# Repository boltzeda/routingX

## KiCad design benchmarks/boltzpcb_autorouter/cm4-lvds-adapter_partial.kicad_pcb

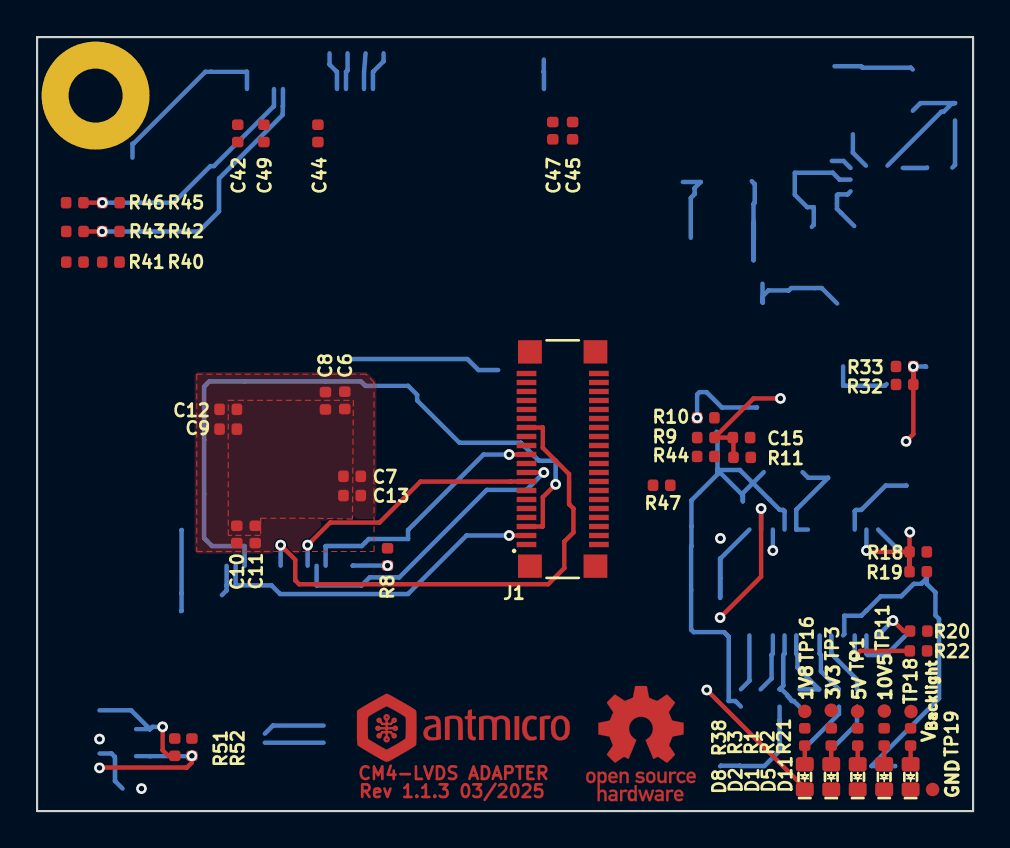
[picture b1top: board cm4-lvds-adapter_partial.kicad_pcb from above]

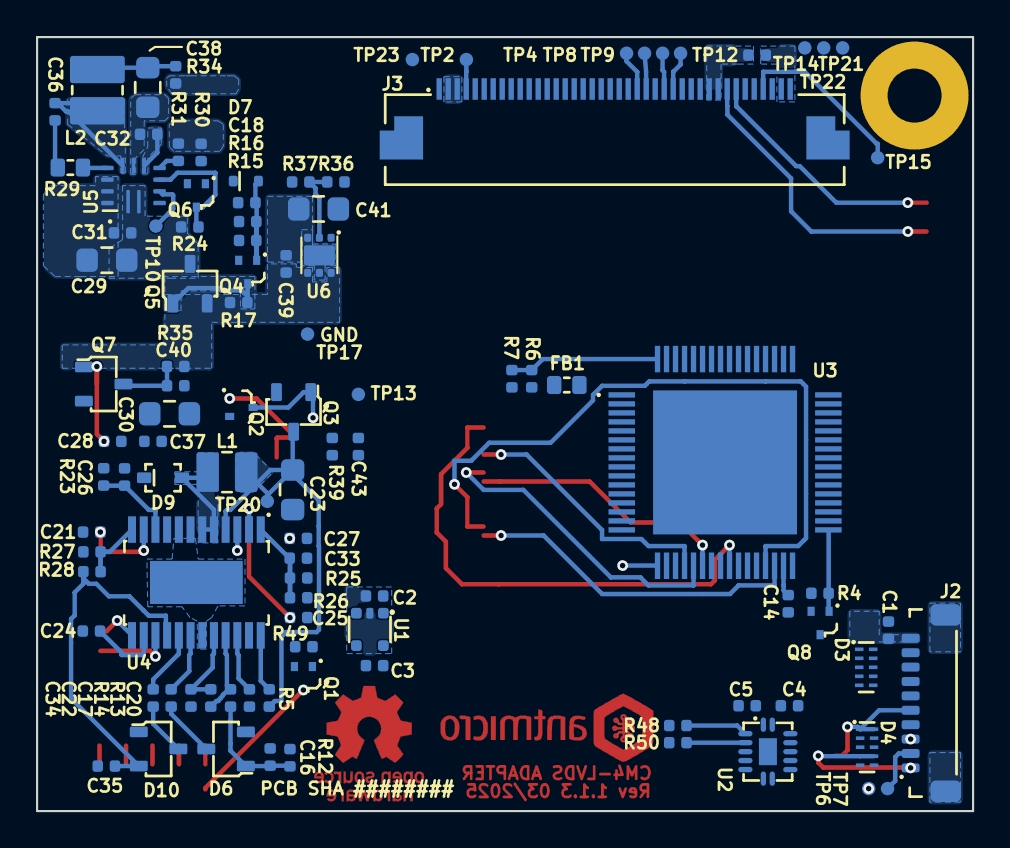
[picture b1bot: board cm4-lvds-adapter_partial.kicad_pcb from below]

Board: 6 copper layers, 52.0 x 43.0 mm, 153 parts (101 on the bottom side), 106 nets.

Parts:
C1, C6, C15: C_10u_0402; C_0402_1005Metric
C2, C3, C7, C14: C_1u_0402; C_0402_1005Metric
C4, C5, C8, C9, C10, C18, C27, C31, C32, C36, C42, C43, C44, C45, C46, C47, C49: C_100n_0402; C_0402_1005Metric
C11, C12, C13, C25: C_10n_0402; C_0402_1005Metric
C16, C22, C34, C35: C_330n_0402; C_0402_1005Metric
C17, C37: C_220n_16V_0402; C_0402_1005Metric
C20: C_2n2_0402; C_0402_1005Metric
C21: C_1n_0402; C_0402_1005Metric
C23, C29, C30, C38, C41: C_22u_25V_0805; C_0805_2012Metric
C24, C33: C_22p_0402; C_0402_1005Metric
C26, C28, C39, C40: C_1u_25V_0402; C_0402_1005Metric
D1, D2, D5, D8, D11: LED_G_0603_KP-1608ZGC; LED_0603_1608Metric_G
D3, D4: PUSB3F96X_PASS; Nexperia_DFN-10_2.5x1mm_P0.5mm
D6, D10: BAT54S-E3-08; SOT-23-3
D7: RB521S30T1G; SOD-523
D9: PMEG3010CEJ,115; D_SOD-323F
FB1: FB_220Z_2.2A_TDK-MPZ_0603; FB_0603_1608Metric
J1: Plug_Molex_SlimStack_2x20_556500488; Conn_Plug_Molex_SlimStack_2x20_556500488
J2: JST_SUR_1x10_SM10B-SURS-TF-LF-SN; Conn_JST_SUR_1x10_SM10B-SURS-TF-LF-SN
J3: FFC_Amphenol_1x40_62684-401100AHLF; Conn_FFC_Amphenol_1x40_62684-401100AHLF
L1: L_3u3_2.5A_1008; L_1008_2520Metric
L2: L_10u_0.5A_Murata-8200; L_Murata-8200
MP1: MP_Pad6mm_Drill3mm
Q1, Q2, Q4, Q6, Q8: PJE138K; SOT-523
Q3, Q5, Q7: SSM3J332R; SOT-23-3
R1, R38: R_470R_0402; R_0402_1005Metric
R2, R21: R_1k5_0402; R_0402_1005Metric
R3: R_100R_0402; R_0402_1005Metric
R4, R10, R11, R17, R26, R33, R44, R49: R_100k_0402; R_0402_1005Metric
R5, R12, R20, R22, R23, R34, R35, R41, R43, R46, R51, R52: R_0R_0402; R_0402_1005Metric
R6, R7, R8, R24, R37, R39, R40, R42, R45, R47, R48, R50: R_10k_0402; R_0402_1005Metric
R9: R_1k_0402; R_0402_1005Metric
R13, R19: R_590k_0402; R_0402_1005Metric
R14: R_120k_0402; R_0402_1005Metric
R15, R30: R_330k_0402; R_0402_1005Metric
R16: R_49k9_0402; R_0402_1005Metric
R18: R_1M_0402; R_0402_1005Metric
R25: R_820k_0402; R_0402_1005Metric
R27, R36: R_110k_0402; R_0402_1005Metric
R28: R_1M5_0402; R_0402_1005Metric
R29: R_20R_0603; R_0603_1608Metric
R31: R_1R2_0402; R_0402_1005Metric
R32: R_510k_0402; R_0402_1005Metric
TP1, TP2, TP3, TP4, TP6, TP7, TP8, TP9, TP10, TP11, TP12, TP13, TP14, TP15, TP16, TP17, TP18, TP19, TP20, TP21, TP22, TP23: TP_0.75mm_SMD; TP_SMD_0.75mm
U1: TLV70018_SC70; SC-70-5
U2: NTS0104_DHVQFN; DHVQFN-14-1EP_2.5x3mm
U3: SN65DSI84; HTQFP-64_10x10mm_P0.5mm
U4: TPS65150_HTSSOP; HTSSOP-24_W4.4mm_P0.65mm
U5: MPQ7235GQBE; QFN-13_2.5x3mm
U6: TLV76701_WSON; WSON-6-1EP_2x2mm_P0.65mm

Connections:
+1V8: C3.2, C5.2, FB1.1, Q1.1 (G), R6.2, R48.2, R49.1, R50.2, TP16.1, U1.5 (VOUT), U2.1 (VCC_A), U2.8 (OE)
+3V3: C2.2, C4.2, C47.2, J1.12, J3.2, J3.3, R3.2, R39.2, R40.2, R42.2, R44.2, R45.2, R47.2, TP3.1, U1.1 (VIN), U2.14 (VCC_B)
+3V9: C45.2, J3.1, R23.2, TP23.1
+5V: C1.2, D3.1 (CH1), D3.10 (CH1), J1.4, J1.6, J1.8, J1.10, J2.10, Q3.2 (S), R1.2, R10.2, R20.2, R38.2, TP1.1
+9V6: C41.1, C44.2, J3.29, R36.2, U6.1 (OUT)
+10V5: C39.2, Q5.2 (S), R2.2, R17.2, R18.2, R35.2, TP11.1, U6.4 (EN), U6.6 (IN)
+18V: C42.2, J3.38, R15.2, R22.2, TP22.1
+VLED: C46.2, J3.39, J3.40, R34.2
-6V: C49.2, J3.35, R12.2, TP21.1
-VLED: C46.1, J3.31, J3.32, R30.1, R31.2
/Antmicro CM4 Baseboard DSI Connector /DSI.CLK_N: J1.27, U3.25 (DACN)
/Antmicro CM4 Baseboard DSI Connector /DSI.CLK_P: J1.29, U3.24 (DACP)
/Antmicro CM4 Baseboard DSI Connector /DSI.D0_N: J1.21, U3.20 (DA0N)
/Antmicro CM4 Baseboard DSI Connector /DSI.D0_P: J1.23, U3.19 (DA0P)
/Antmicro CM4 Baseboard DSI Connector /DSI.D1_N: J1.15, U3.22 (DA1N)
/Antmicro CM4 Baseboard DSI Connector /DSI.D1_P: J1.17, U3.21 (DA1P)
/Antmicro CM4 Baseboard DSI Connector /DSI.D2_N: J1.9, U3.28 (DA2N)
/Antmicro CM4 Baseboard DSI Connector /DSI.D2_P: J1.11, U3.27 (DA2P)
/Antmicro CM4 Baseboard DSI Connector /DSI.D3_N: J1.3, U3.30 (DA3N)
/Antmicro CM4 Baseboard DSI Connector /DSI.D3_P: J1.5, U3.29 (DA3P)
/Antmicro CM4 Baseboard DSI Connector /DSICtrl.DIM: J1.28, Q6.1 (G)
/Antmicro CM4 Baseboard DSI Connector /DSICtrl.EN: D7.1 (C), J1.24, J3.6, R9.1, R44.1, U1.3 (EN), U2.11 (B3)
/Antmicro CM4 Baseboard DSI Connector /DSICtrl.GPIO: D4.2 (CH2), D4.9 (CH2), J1.30, J2.4
/Antmicro CM4 Baseboard DSI Connector /DSICtrl.SCL: D3.2 (CH2), D3.9 (CH2), J1.18, J2.9, U2.12 (B2)
/Antmicro CM4 Baseboard DSI Connector /DSICtrl.SDA: D3.4 (CH3), D3.7 (CH3), J1.16, J2.8, U2.13 (B1)
/Antmicro CM4 Baseboard DSI Connector /DSICtrl.~IRQ1: J1.20, Q8.3 (D), R47.1
/Antmicro CM4 Baseboard DSI Connector /DSICtrl.~IRQ2: D3.5 (CH4), D3.6 (CH4), J1.22, J2.7
/Antmicro CM4 Baseboard DSI Connector /DSICtrl.~RST: C43.2, J1.26, J3.5, R39.1, R51.1, R52.1, TP13.1
/DSI to LVDS/DSICtrl_1V8.EN: U2.4 (A3), U3.2 (EN)
/DSI to LVDS/DSICtrl_1V8.SCL: R50.1, U2.3 (A2), U3.15 (SCL)
/DSI to LVDS/DSICtrl_1V8.SDA: R48.1, U2.2 (A1), U3.16 (SDA)
/DSI to LVDS/LVDS.CLK_N: J3.17, U3.39 (A_CLKN)
/DSI to LVDS/LVDS.CLK_P: J3.18, U3.38 (A_CLKP)
/DSI to LVDS/LVDS.D0_N: J3.8, U3.47 (A_Y0N)
/DSI to LVDS/LVDS.D0_P: J3.9, U3.46 (A_Y0P)
/DSI to LVDS/LVDS.D1_N: J3.11, U3.45 (A_Y1N)
/DSI to LVDS/LVDS.D1_P: J3.12, U3.44 (A_Y1P)
/DSI to LVDS/LVDS.D2_N: J3.14, U3.42 (A_Y2N)
/DSI to LVDS/LVDS.D2_P: J3.15, U3.41 (A_Y2P)
/DSI to LVDS/LVDS.D3_N: J3.20, U3.37 (A_Y3N)
/DSI to LVDS/LVDS.D3_P: J3.21, U3.36 (A_Y3P)
/LVDS and Touchscreen Connectors/RST_TS: D4.1 (CH1), D4.10 (CH1), J2.5, R51.2
/LVDS and Touchscreen Connectors/SELB: J3.28, R40.1, R41.1
/LVDS and Touchscreen Connectors/SHLR: J3.33, R42.1, R43.1
/LVDS and Touchscreen Connectors/TP10_TS: D4.4 (CH3), D4.7 (CH3), J2.1, R52.2
/LVDS and Touchscreen Connectors/UPDN: J3.34, R45.1, R46.1
/Power/ADJ: C24.2, U4.14 (ADJ)
/Power/COMP: C20.2, U4.22 (COMP)
/Power/DLY1: C25.2, U4.2 (DLY1)
/Power/DLY2: C27.2, U4.3 (DLY2)
/Power/FDLY: R5.2, U4.24 (FDLY)
/Power/FLK: R20.1, U4.13 (CTRL)
/Power/Vi_{BOOST}: C23.1, L1.1, Q3.3 (D), R5.1, TP20.1, U4.4 (VIN)
GND: C1.1, C2.1, C3.1, C4.1, C5.1, C6.1, C7.1, C8.1, C9.1, C10.1, C11.1, C12.1, C13.1, C14.1, C15.1, C16.1, C17.1, C18.1, C20.1, C21.1, C23.2, C24.1, C25.1, C26.1, C27.1, C28.1, C29.2, C30.2, C31.1, C32.1, C35.1, C38.2, C39.1, C40.1, C41.2, C42.1, C43.1, C44.1, C45.1, C47.1, C49.1, D1.1 (C), D2.1 (C), D3.3 (GND), D3.8 (GND), D4.3 (GND), D4.5 (CH4), D4.6 (CH4), D4.8 (GND), D5.1 (C), D6.2, D11.1 (C), J1.1, J1.2, J1.7, J1.13, J1.14, J1.19, J1.25, J1.31, J1.32, J1.MP, J2.6, J2.MP, J3.7, J3.10, J3.13, J3.16, J3.19, J3.22, J3.25, J3.30, J3.SH, MP1.1, Q1.2 (S), Q2.2 (S), Q4.2 (S), Q6.2 (S), Q8.2 (S), R4.2, R7.1, R8.2, R11.1, R16.1, R19.1, R26.1, R27.1, R31.1, R37.1, R41.2, R43.2, R46.2, R49.2, TP17.1, TP19.1, U1.2 (GND), U2.7 (GND), U2.15 (GNDPAD), U3.23 (GND), U3.26 (GND), U3.52 (GND), U3.65 (PAD), U4.7 (PGND), U4.8 (PGND), U4.19 (AGND), U4.25 (EP), U5.8 (GND), U5.11 (GND), U5.12 (GND), U5.13 (GND), U6.3 (GND), U6.5 (GND), U6.7 (PAD)
unnamed: C6.2, C7.2, C8.2, C9.2, C10.2, C11.2, C12.2, C13.2, FB1.2, U3.3 (VCC), U3.14 (VCC), U3.18 (VCC), U3.32 (VCC), U3.35 (VCC), U3.40 (VCC), U3.43 (VCC), U3.48 (VCC), U3.49 (VCC), U3.55 (VCC), U3.58 (VCC), U3.63 (VCC)
unnamed: C16.2, D6.1, R12.1, R13.2
unnamed: C22.2, D6.3
unnamed: C34.1, D10.3
unnamed: C36.2, R29.2
unnamed: C38.1, L2.2, R34.1
unnamed: D1.2 (A), R1.1
unnamed: D2.2 (A), R3.1
unnamed: D5.2 (A), R2.1
unnamed: C18.2, D7.2 (A), Q4.1 (G), R15.1, R16.2
unnamed: D8.2 (A), R38.1
unnamed: D8.1 (C), Q1.3 (D)
unnamed: D9.2 (A), L1.2, U4.5 (SW), U4.6 (SW)
unnamed: C28.2, C30.1, C33.2, C37.2, D9.1 (C), D10.1, Q7.2 (S), R25.2, R32.2, U4.9 (SUP)
unnamed: D11.2 (A), R21.1
unnamed: J2.2, TP7.1
unnamed: J2.3, TP6.1
unnamed: J3.4, TP2.1
unnamed: J3.23, TP4.1
unnamed: J3.24, TP8.1
unnamed: J3.26, TP9.1
unnamed: J3.27, TP12.1
unnamed: J3.36, TP14.1
unnamed: J3.37, TP15.1
unnamed: Q2.3 (D), Q3.1 (G), R10.1
unnamed: C15.2, Q2.1 (G), R9.2, R11.2
unnamed: Q4.3 (D), Q5.1 (G), R17.1
unnamed: C29.1, C31.2, Q5.3 (D), R21.2, R24.2, TP18.1, U5.1 (IN), U5.2 (IN)
unnamed: Q6.3 (D), R24.1, U5.5 (DIM)
unnamed: C40.2, Q7.3 (D), R35.1
unnamed: C37.1, Q7.1 (G), R32.1, R33.2
unnamed: Q8.1 (G), R4.1, U3.33 (IRQ)
unnamed: R6.1, R7.2, U3.64 (ADDR)
unnamed: R8.1, U3.17 (REFCLK)
unnamed: C14.2, U3.31 (VCORE)
unnamed: C35.2, D10.2, R28.2, U4.16 (CPI)
unnamed: C22.1, U4.18 (DRVN)
unnamed: C34.2, U4.17 (DRVP)
unnamed: C33.1, R25.1, R26.2, U4.1 (FB)
unnamed: R13.1, R14.2, U4.21 (FBN)
unnamed: R27.2, R28.1, U4.12 (FBP)
unnamed: R33.1, U4.23 (GD)
unnamed: C21.2, R18.1, R19.2, U4.11 (IN)
unnamed: C17.2, R14.1, U4.20 (REF)
unnamed: C26.2, R23.1, U4.10 (VCOM)
unnamed: R22.1, U4.15 (VGH)
unnamed: R29.1, U5.10 (BST)
unnamed: R30.2, U5.6 (FB)
unnamed: C36.1, L2.1, U5.9 (SW)
unnamed: C32.2, U5.7 (V_{CC})
unnamed: TP10.1, U5.4 (~FAULT)
unnamed: R36.1, R37.2, U6.2 (FB)

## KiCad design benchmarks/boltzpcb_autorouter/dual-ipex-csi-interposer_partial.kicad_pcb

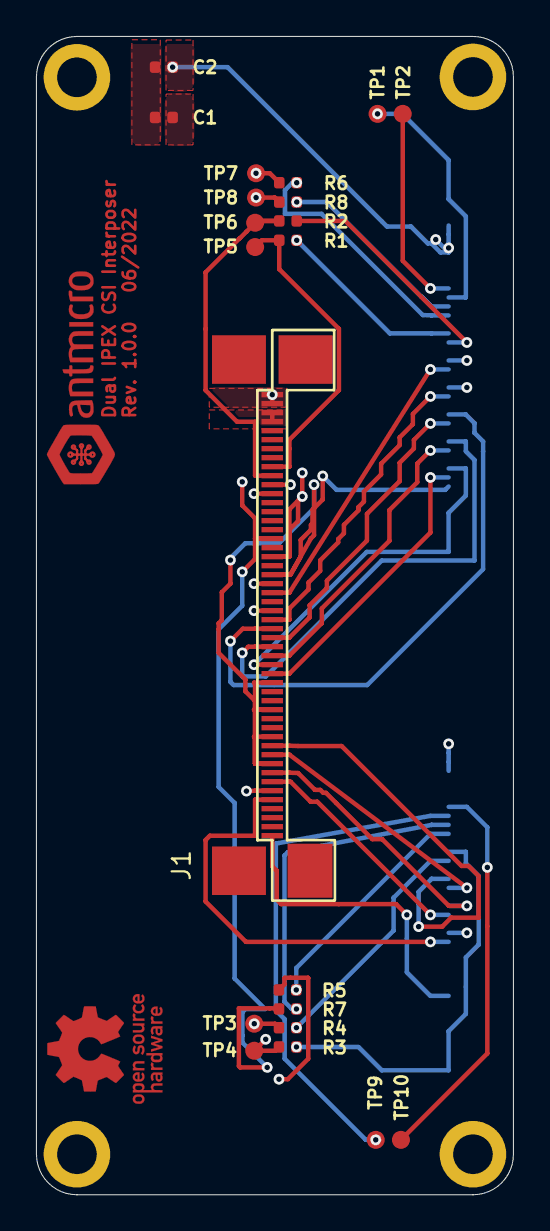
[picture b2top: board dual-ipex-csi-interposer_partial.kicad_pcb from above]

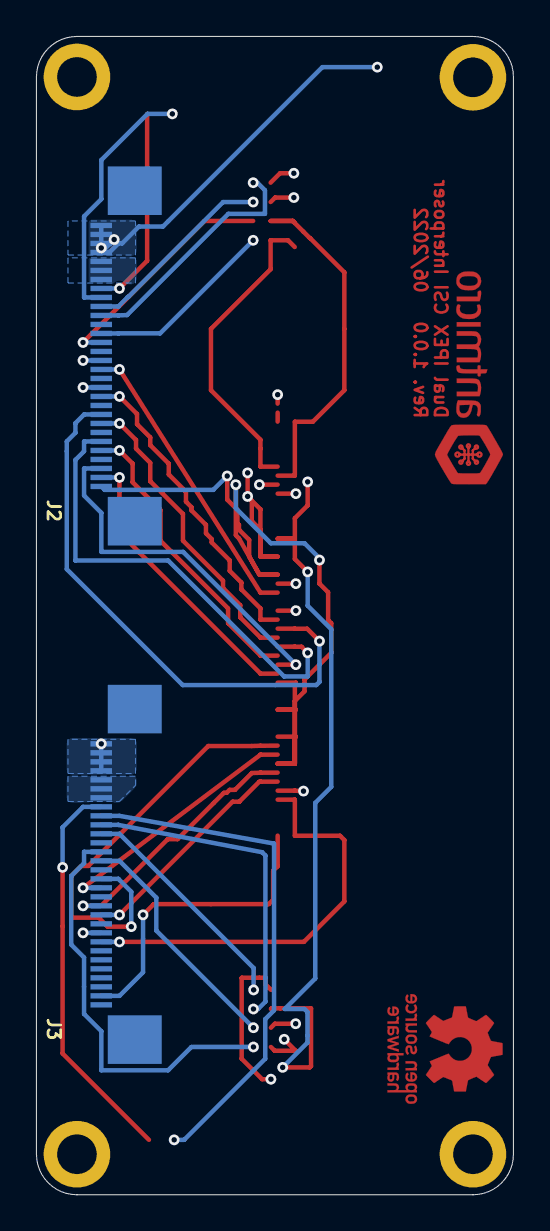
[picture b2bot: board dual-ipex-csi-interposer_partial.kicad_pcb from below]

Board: 4 copper layers, 26.5 x 64.3 mm, 29 parts (2 on the bottom side), 41 nets.

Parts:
C1, C2: C_100n_0402; 0402-cap
J1: WE_68715014522
J2, J3: MSAK24025P30
MP1, MP2, MP3, MP4: PCB_Mount_Hole_2.2_4.5; mounting-hole-2.2mm
N1: oshw_logo; oshw-logo
N2: antmicro_logo; antmicro-logo_scaled_12mm
R1, R2, R3, R4, R5, R6, R7, R8: R_0R_0402; 0402-res
TP1, TP2, TP3, TP4, TP5, TP6, TP7, TP8, TP9, TP10: TP_SMD1MM; Testpoint_smd_1mm

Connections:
3V3_FFC: C1.1, J1.47, J1.48, J2.24, J2.25, J2.26, J3.24, J3.25, J3.26
5V0_SYS: C2.1, J1.49, J1.50, J2.27, J2.28, J2.29, J2.30, J3.27, J3.28, J3.29, J3.30
/CAM_CSI_CAM_EN: J1.32, R5.2, R6.2, TP7.1
/CAM_CSI_CAM_XVS: J1.34, R7.2, R8.2, TP8.1
/CAM_L_SCL: J1.40, R3.2, TP4.1
/CAM_L_SDA: J1.39, R4.2, TP3.1
/CAM_R_SCL: J1.42, R1.2, TP5.1
/CAM_R_SDA: J1.41, R2.2, TP6.1
CAM1_CSI_CAM_CLK: J2.22, TP1.1
CAM1_CSI_CAM_EN: J2.20, R6.1
CAM1_CSI_CAM_XTRIG: J2.23, TP2.1
CAM1_CSI_CAM_XVS: J2.21, R8.1
CAM1_CSI_CLK_N: J1.28, J2.14
CAM1_CSI_CLK_P: J1.29, J2.15
CAM1_CSI_D0_N: J1.25, J2.11
CAM1_CSI_D0_P: J1.26, J2.12
CAM1_CSI_D1_N: J1.23, J2.8
CAM1_CSI_D1_P: J1.24, J2.9
CAM1_CSI_D2_N: J1.21, J2.5
CAM1_CSI_D2_P: J1.22, J2.6
CAM1_CSI_D3_N: J1.19, J2.2
CAM1_CSI_D3_P: J1.20, J2.3
CAM1_SCL: J2.18, R1.1
CAM1_SDA: J2.17, R2.1
CAM2_CSI_CAM_CLK: J3.22, TP9.1
CAM2_CSI_CAM_EN: J3.20, R5.1
CAM2_CSI_CAM_XTRIG: J3.23, TP10.1
CAM2_CSI_CAM_XVS: J3.21, R7.1
CAM2_CSI_CLK_N: J1.10, J3.14
CAM2_CSI_CLK_P: J1.11, J3.15
CAM2_CSI_D0_N: J1.7, J3.11
CAM2_CSI_D0_P: J1.8, J3.12
CAM2_CSI_D1_N: J1.5, J3.8
CAM2_CSI_D1_P: J1.6, J3.9
CAM2_CSI_D2_N: J1.3, J3.5
CAM2_CSI_D2_P: J1.4, J3.6
CAM2_CSI_D3_N: J1.1, J3.2
CAM2_CSI_D3_P: J1.2, J3.3
CAM2_SCL: J3.18, R3.1
CAM2_SDA: J3.17, R4.1
GND: C1.2, C2.2, J1.9, J1.12, J1.15, J1.18, J1.27, J1.30, J2.1, J2.4, J2.7, J2.10, J2.13, J2.16, J2.19, J3.1, J3.4, J3.7, J3.10, J3.13, J3.16, J3.19

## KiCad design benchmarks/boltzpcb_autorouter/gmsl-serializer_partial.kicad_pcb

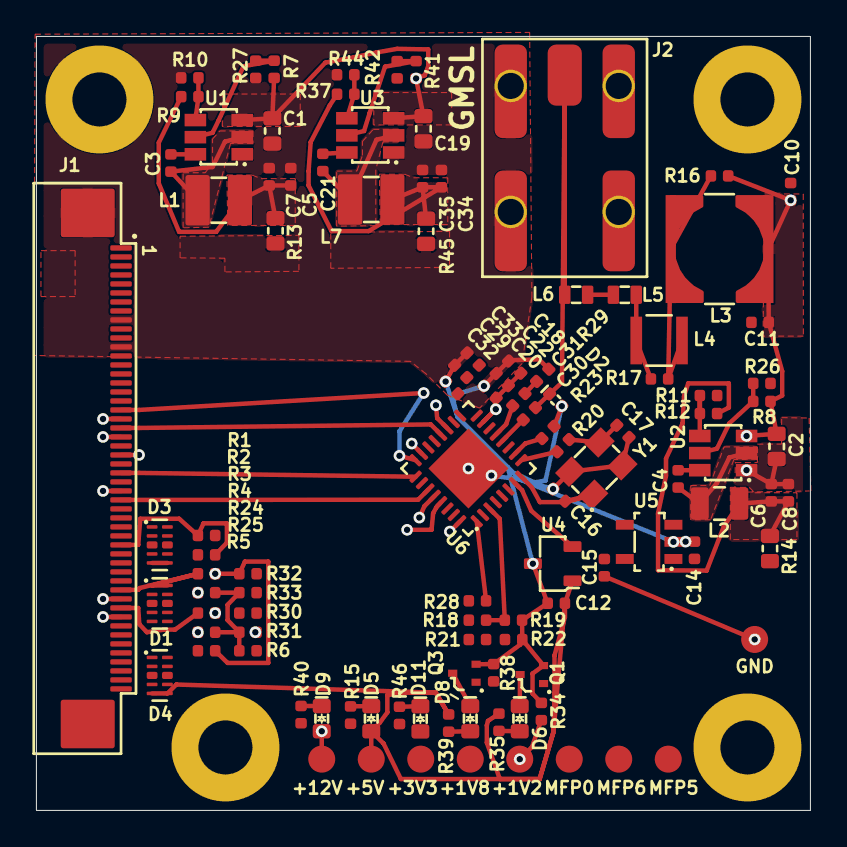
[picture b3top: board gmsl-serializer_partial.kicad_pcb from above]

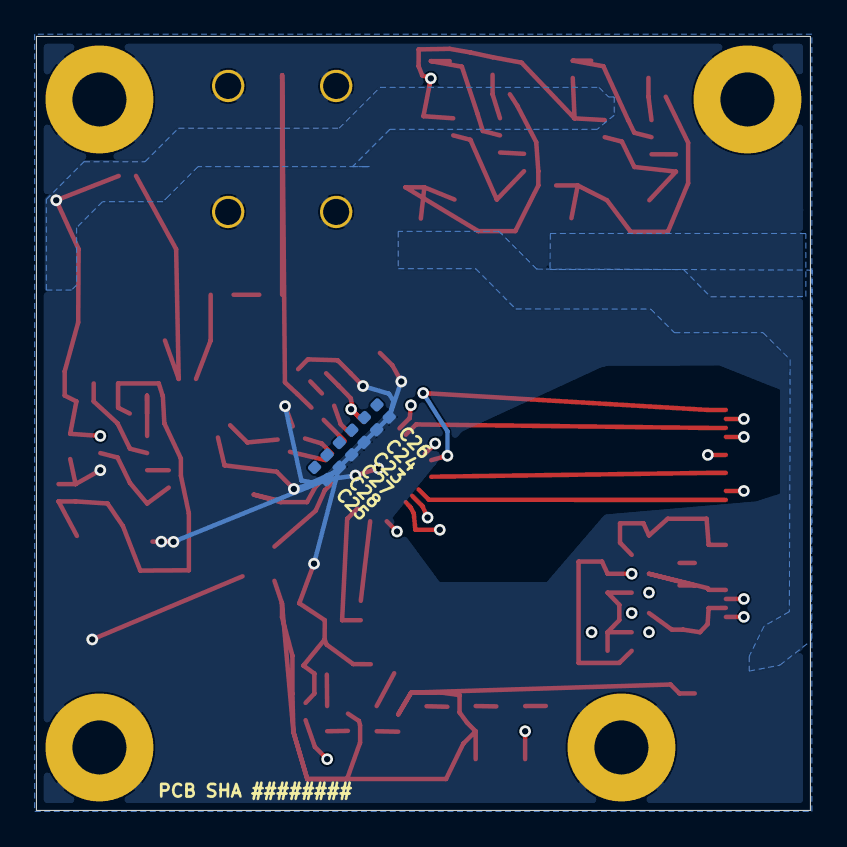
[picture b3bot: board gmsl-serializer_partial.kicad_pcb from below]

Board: 4 copper layers, 43.0 x 43.0 mm, 118 parts (6 on the bottom side), 70 nets.

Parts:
C1, C2, C19: C_10u_25V_0603; C_0603_1608Metric
C3, C21: C_220n_0402; C_0402_1005Metric
C4, C10, C20, C22, C24, C30, C31: C_100n_0402; C_0402_1005Metric
C5, C6, C7, C8, C34, C35: C_22u_0402; C_0402_1005Metric
C11, C23, C27, C28, C29, C32: C_10n_0402; C_0402_1005Metric
C12, C14, C15: C_1u_16V_0402; C_0402_1005Metric
C16, C17: C_33p_0402; C_0402_1005Metric
C18, C25, C26, C33: C_10u_0402; C_0402_1005Metric
D1, D3, D4: PESD4USB5U-TTS; DFN-10_2.5x1mm
D2: AXGD10402KR; D_0402_1005Metric
D5, D6, D8, D9, D11: LED_G_0603_LTST-C190GKT; LED_0603_1608Metric_G
J1: Conn_FFC_WE_68715014022; Conn_FFC_WE_68715014x22
J2: Conn_FAKRA_59S2AQ-40MT5-Z_1
L1, L7: L_3u3_3.1A_Bourns-SRP3212A; L_Bourns-SRP3212A
L2: L_1u_2.6A_0806; L_0806_2016Metric
L3: L_22u_1.12A_Coilcraft-MSS6132T; L_Coilcraft-MSS6132T
L4: L_6u8_1A_Coilcraft-1210POC; L_Coilcraft-1210POC
L5, L6: L_470n_1A_Coilcraft-PFL1609; L_Coilcraft-PFL1609
MP1, MP2, MP3, MP4: MP_Pad6mm_Drill3mm
N1: antmicro_logo; antmicro-logo_scaled_12mm_mask
Q1, Q3: DMG1012T-7; SOT-523
R1, R7, R8, R10, R12, R19, R21, R22, R26, R27, R28, R41, R42, R44: R_10k_0402; R_0402_1005Metric
R2: R_12k_0402; R_0402_1005Metric
R3, R4, R24, R25: R_100R_0402; R_0402_1005Metric
R5, R6: R_4k7_0402; R_0402_1005Metric
R9: R_52k3_0402; R_0402_1005Metric
R11: R_12k4_0402; R_0402_1005Metric
R13, R14, R45: R_0R_22.4A_0603; R_0603_1608Metric
R15, R35, R39: R_470R_0402; R_0402_1005Metric
R16, R17: R_5k1_0402; R_0402_1005Metric
R18: R_80k6_0402; R_0402_1005Metric
R20, R30, R31, R32, R33: R_0R_0402; R_0402_1005Metric
R23: R_402R_0402; R_0402_1005Metric
R29: R_51R_0402; R_0402_1005Metric
R34, R38: R_100k_0402; R_0402_1005Metric
R37: R_31k6_0402; R_0402_1005Metric
R40: R_1k65_0402; R_0402_1005Metric
R46: R_200R_0402; R_0402_1005Metric
TP1, TP2, TP3, TP4, TP5, TP6, TP7, TP8, TP9: TP_1.5mm_SMD; TP_SMD_1.5mm
U1, U2, U3: AP62301_TSOT; TSOT23-6
U4: REF3012AIDBZT; SOT-23-3
U5: TLV73312PDBVT; SOT-23-5
U6: MAX96717GTJ_VY+; TQFN-32-1EP_5x5mm_P0.5mm
Y1: Resonator_25MHz_ABM8G; Resonator_SMD_Abracon_ABM8G_3.2x2.5mm

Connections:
+1V2: C15.2, C18.2, C20.2, C22.2, Q1.1 (G), R34.2, TP5.1, U5.5 (VOUT), U6.15 (VDD)
+1V8: C14.2, C25.2, C27.2, C28.2, Q3.1 (G), R14.2, R38.2, TP2.1, U5.1 (VIN), U5.3 (EN), U6.11 (VDD18)
+3V3: C29.2, C32.2, C33.2, D4.1, D4.2, D4.9, D4.10, D11.2 (A), J1.47, J1.48, R5.2, R6.2, R18.2, R21.2, R28.2, R45.2, TP4.1, U6.16 (VDDIO)
+5V: C12.2, D4.4, D4.5, D4.6, D4.7, D5.2 (A), J1.49, J1.50, R13.2, R35.2, R39.2, TP1.1, U4.1 (IN)
+12V: C1.2, C2.2, C10.2, C11.2, C19.2, D9.2 (A), L3.1, R7.2, R8.2, R16.1, R41.2, TP3.1, U1.3 (VIN), U2.3 (VIN), U3.3 (VIN)
/CSI Connector/CSI.CLK_N: J1.28, U6.28 (CKN)
/CSI Connector/CSI.CLK_P: J1.29, U6.27 (CKP)
/CSI Connector/CSI.D0_N: J1.25, U6.26 (D0N)
/CSI Connector/CSI.D0_P: J1.26, U6.25 (D0P)
/CSI Connector/CSI.D1_N: J1.23, U6.30 (D1N)
/CSI Connector/CSI.D1_P: J1.24, U6.29 (D1P)
/CSI Connector/CSI.D2_N: J1.21, U6.20 (D2N)
/CSI Connector/CSI.D2_P: J1.22, U6.19 (D2P)
/CSI Connector/CSI.D3_N: J1.19, U6.24 (D3N)
/CSI Connector/CSI.D3_P: J1.20, U6.23 (D3P)
/CSI Connector/GPIO3: D3.1, D3.10, J1.32, U6.17 (MFP3)
/CSI Connector/GPIO4: R1.2, U6.18 (MFP4)
/CSI Connector/GPIO4_1V8: D3.2, D3.9, J1.34, R1.1, R2.1
/CSI Connector/I2C.SCL: R4.2, R6.1, R25.2, R31.1, R33.1
/CSI Connector/I2C.SDA: R3.2, R5.1, R24.2, R30.1, R32.1
/CSI Connector/SCL_CAM0: D1.2, D1.9, J1.40, R4.1
/CSI Connector/SCL_CAM1: D1.5, D1.6, J1.42, R25.1
/CSI Connector/SDA_CAM0: D1.1, D1.10, J1.39, R3.1
/CSI Connector/SDA_CAM1: D1.4, D1.7, J1.41, R24.1
/GMSL Connector/SIO_P: C30.2, D2.1 (C), J2.1, L6.2
/Serializer/CFG0: R18.1, R19.2, U6.3 (MFP1)
/Serializer/CFG1: R21.1, R22.2, U6.4 (MFP2)
/Serializer/VREF: U4.2 (OUT), U6.7 (VREF)
/Serializer/X1: C16.2, U6.8 (X1/OSC), Y1.1
/Serializer/X2: R20.2, U6.9 (X2)
/Serializer/X2_R: C17.2, R20.1, Y1.3
/Supply/EN_1V8: R8.1, R26.2, U2.5 (EN)
/Supply/EN_3V3: R41.1, R42.2, U3.5 (EN)
/Supply/EN_5V: R7.1, R27.2, U1.5 (EN)
/Supply/FB_1V8: R11.1, R12.2, U2.4 (FB)
/Supply/FB_3V3: R37.1, R44.2, U3.4 (FB)
/Supply/FB_5V: R9.1, R10.2, U1.4 (FB)
/Supply/OUT_1V8: C6.2, C8.2, L2.2, R11.2, R14.1
/Supply/OUT_3V3: C34.2, C35.2, L7.2, R37.2, R45.1
/Supply/OUT_5V: C5.2, C7.2, L1.2, R9.2, R13.1
/Supply/SW_1V8: C4.2, L2.1, U2.2 (SW)
/Supply/SW_3V3: C21.2, L7.1, U3.2 (SW)
/Supply/SW_5V: C3.2, L1.1, U1.2 (SW)
GND: C1.1, C2.1, C5.1, C6.1, C7.1, C8.1, C10.1, C11.1, C12.1, C14.1, C15.1, C16.1, C17.1, C18.1, C19.1, C20.1, C22.1, C23.1, C24.1, C25.1, C26.1, C27.1, C28.1, C29.1, C32.1, C33.1, C34.1, C35.1, D1.3, D1.8, D2.2 (A), D3.3, D3.8, D4.3, D4.8, J1.9, J1.12, J1.15, J1.18, J1.27, J1.30, J1.MP1 (MP), J1.MP2 (MP), J2.2, J2.3, J2.4, J2.5, MP1.1, MP2.1, MP3.1, MP4.1, Q1.2 (S), Q3.2 (S), R2.2, R10.1, R12.1, R15.1, R19.1, R22.1, R23.1, R26.1, R27.1, R29.1, R34.1, R38.1, R40.1, R42.1, R44.1, R46.1, TP9.1, U1.1 (GND), U2.1 (GND), U3.1 (GND), U4.3 (GND), U5.2 (GND), U6.33 (GND), Y1.2 (SH), Y1.4 (SH)
unnamed: C31.2, R29.2
unnamed: D5.1 (C), R15.2
unnamed: D6.2 (A), R35.1
unnamed: D6.1 (C), Q1.3 (D)
unnamed: D8.2 (A), R39.1
unnamed: D8.1 (C), Q3.3 (D)
unnamed: D9.1 (C), R40.2
unnamed: D11.1 (C), R46.2
unnamed: L3.2, L4.1, R16.2, R17.1
unnamed: L4.2, L5.1, R17.2
unnamed: L5.2, L6.1
unnamed: C3.1, U1.6 (BST)
unnamed: C4.1, U2.6 (BST)
unnamed: C21.1, U3.6 (BST)
unnamed: C23.2, C24.2, C26.2, U6.14 (CAP_VDD)
unnamed: TP6.1, U6.2 (MFP0)
unnamed: TP7.1, U6.21 (MFP5)
unnamed: TP8.1, U6.22 (MFP6)
unnamed: R30.2, U6.31 (MFP7)
unnamed: R31.2, U6.32 (MFP8)
unnamed: R32.2, U6.5 (MFP9)
unnamed: R33.2, U6.6 (MFP10)
unnamed: R28.1, U6.1 (PWDNB)
unnamed: C31.1, U6.13 (SION)
unnamed: C30.1, U6.12 (SIOP)
unnamed: R23.2, U6.10 (XRES)

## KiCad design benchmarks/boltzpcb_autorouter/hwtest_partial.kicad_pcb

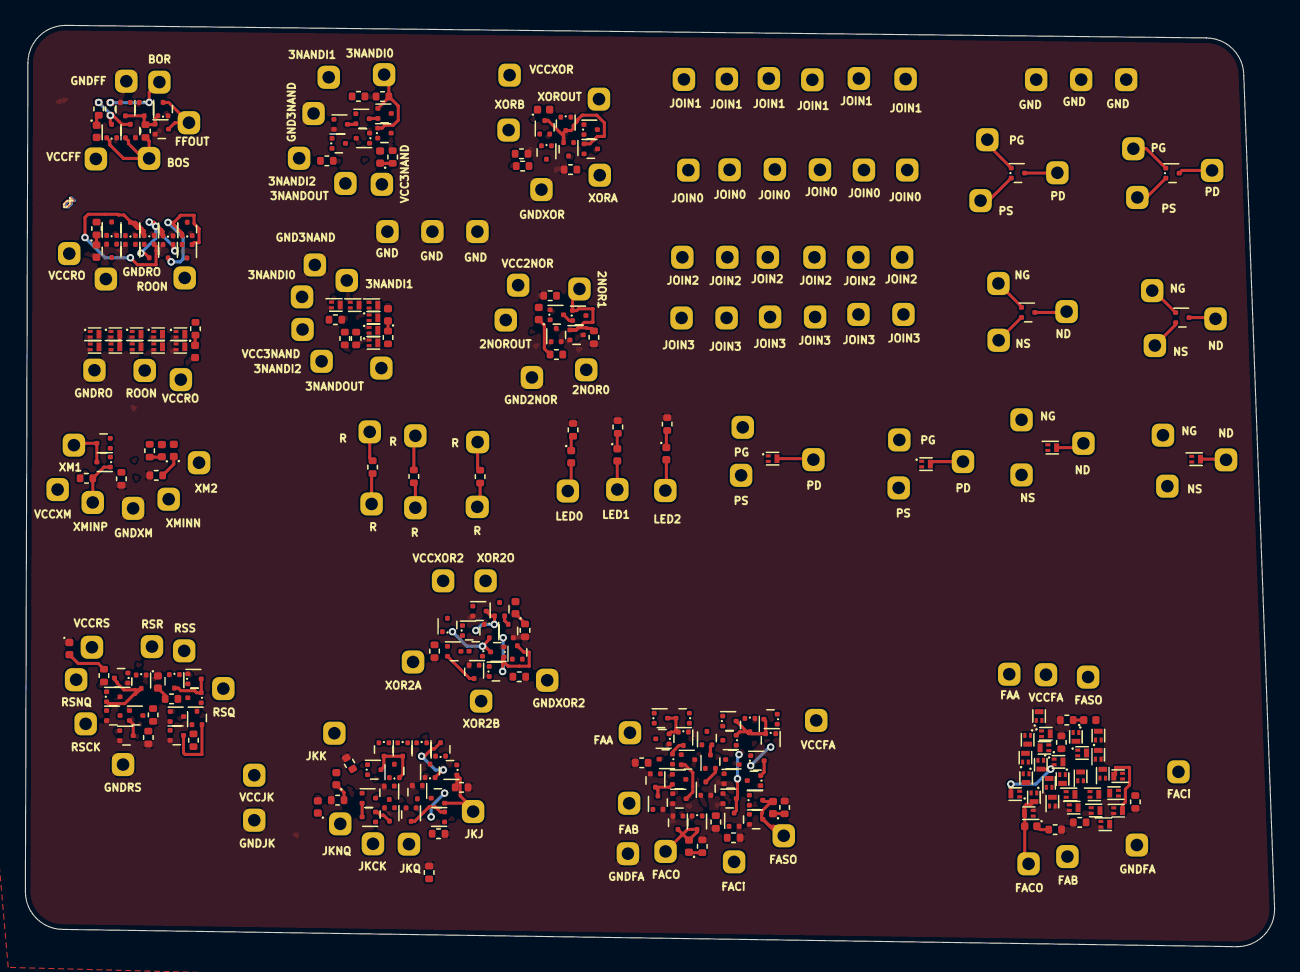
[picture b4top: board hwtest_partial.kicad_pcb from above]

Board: 2 copper layers, 99.7 x 73.5 mm, 362 parts (0 on the bottom side), 161 nets.

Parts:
D1, D2, D3, D4, D5, D6, D7, D8, D9, D10, D11, D12, D13, D14, D15, D16, D17, D18, D19, D20, D21: LED; LED_0402_1005Metric_COMPACT
N1, N2, N3, N4, N5, N6, N7, N8, N14, N15, N16, N20, N21, N22, N23, N24, N25, N26, N27, N30, N31, N32, N33, N34, N35, N36, N37, N38, N39, N40, N41, N42, N43, N44, N45, N46, N47, N48, N49, N50, N51, N52, N53, N54, N55, N56, N57, N58, N59, N60, N61, N62, N63: 2SK3541; SOT-723-COMPACT
N9, N10, N11, N12, N13, N17, N18, N19, N28, N29: NX7002BKMB315; DFN1006-3-NCH
N64, N65, N66, N67, N68, N69, N70, N71, N72, N73, N74, N75, N76, N77: 2SK3541; DFN1006-3-NCH
P1, P2, P3, P4, P5, P6, P7, P8, P14, P15, P16, P20, P21, P22, P23, P24, P25, P26, P27, P30, P31, P32, P33, P34, P35, P36, P37, P38, P39, P40, P41, P42, P43, P44, P45, P46, P47, P48, P49, P50, P51, P52, P53, P54, P55, P56, P57, P58, P59, P60, P61, P62, P63: RZM001P02T2L; SOT-723-COMPACTP
P9, P10, P11, P12, P13, P17, P18, P19, P28, P29: BSS84KNC; DFN1006-3-PCH
P64, P65, P66, P67, P68, P69, P70, P71, P72, P73, P74, P75, P76, P77: RZM001P02T2L; DFN1006-3-PCH
R1, R2, R3, R4, R5, R6, R7, R8, R9, R10, R11, R12, R13, R14, R15, R16, R17, R18, R19, R20, R21, R22, R23, R24, R25, R26, R27, R28, R29, R30, R31, R32, R33, R34, R35, R36, R37, R38, R39, R40, R41, R42, R43, R44, R45, R46, R47, R48, R49, R50, R51, R52: 1k; R_0402_1005Metric_COMPACT
TP1: BOS; TPTHRU
TP2: BOR; TPTHRU
TP3: FFOUT; TPTHRU
TP4, TP11: ROON; TPTHRU
TP5: VCCFF; TPTHRU
TP6: GNDFF; TPTHRU
TP7, TP9: GNDRO; TPTHRU
TP8, TP10: VCCRO; TPTHRU
TP12, TP21: 3NANDOUT; TPTHRU
TP13, TP19: 3NANDI0; TPTHRU
TP14, TP18: 3NANDI1; TPTHRU
TP15, TP20: 3NANDI2; TPTHRU
TP16, TP22: VCC3NAND; TPTHRU
TP17, TP23: GND3NAND; TPTHRU
TP24: 2NOR1; TPTHRU
TP25: 2NOR0; TPTHRU
TP26: 2NOROUT; TPTHRU
TP27: VCC2NOR; TPTHRU
TP28: GND2NOR; TPTHRU
TP29: XORB; TPTHRU
TP30: XM1; TPTHRU
TP31: XM2; TPTHRU
TP32: XMINP; TPTHRU
TP33: XMINN; TPTHRU
TP34: XORA; TPTHRU
TP35: VCCXM; TPTHRU
TP36: GNDXM; TPTHRU
TP37: XOROUT; TPTHRU
TP38: VCCXOR; TPTHRU
TP39: GNDXOR; TPTHRU
TP40: LED0; TPTHRU
TP41: LED1; TPTHRU
TP42: LED2; TPTHRU
TP43, TP68, TP74, TP80: PS; TPTHRU
TP44, TP67, TP73, TP79: PG; TPTHRU
TP45, TP69, TP75, TP81: PD; TPTHRU
TP46, TP71, TP77, TP83: ND; TPTHRU
TP47, TP72, TP78, TP84: NS; TPTHRU
TP48, TP70, TP76, TP82: NG; TPTHRU
TP49, TP50, TP51, TP52, TP53, TP54: R; TPTHRU
TP55, TP56, TP57, TP58, TP59, TP60: JOIN0; TPTHRU
TP61, TP62, TP63, TP64, TP65, TP66: JOIN1; TPTHRU
TP85, TP86, TP87, TP88, TP89, TP90: JOIN2; TPTHRU
TP91, TP92, TP93, TP94, TP95, TP96: JOIN3; TPTHRU
TP97, TP98, TP99, TP100, TP101, TP102: GND; TPTHRU
TP103: JKCK; TPTHRU
TP104: JKQ; TPTHRU
TP105: JKNQ; TPTHRU
TP106: RSNQ; TPTHRU
TP107: RSQ; TPTHRU
TP108: RSR; TPTHRU
TP109: RSS; TPTHRU
TP110: RSCK; TPTHRU
TP111: GNDRS; TPTHRU
TP112: VCCRS; TPTHRU
TP113: JKK; TPTHRU
TP114: JKJ; TPTHRU
TP115: VCCJK; TPTHRU
TP116: GNDJK; TPTHRU
TP117, TP132: FACO; TPTHRU
TP118, TP133: FASO; TPTHRU
TP119, TP129: FACi; TPTHRU
TP120, TP130: FAB; TPTHRU
TP121, TP131: FAA; TPTHRU
TP122, TP134: VCCFA; TPTHRU
TP123, TP135: GNDFA; TPTHRU
TP124: XOR2A; TPTHRU
TP125: XOR2B; TPTHRU
TP126: XOR2O; TPTHRU
TP127: VCCXOR2; TPTHRU
TP128: GNDXOR2; TPTHRU

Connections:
B0NQ: N1.3 (D), P1.3 (D), R1.1, R3.2
B0Q: N2.3 (D), N3.1 (G), P2.3 (D), P3.1 (G), R2.1
B0R: N2.1 (G), P2.1 (G), R1.2, TP2.1
B0S: N1.1 (G), P1.1 (G), R2.2, TP1.1
COUT: D17.2 (A), N57.3 (D), P57.3 (D), TP117.1
COUTs: D20.2 (A), N67.3 (D), P67.3 (D), TP132.1
FAA: N30.1 (G), N41.1 (G), N52.1 (G), N55.1 (G), P30.1 (G), P32.1 (G), P52.1 (G), P53.1 (G), R42.1, TP121.1
FAAs: N66.1 (G), N68.1 (G), N70.1 (G), N73.1 (G), P64.1 (G), P66.1 (G), P72.1 (G), P73.1 (G), R50.1, TP131.1
FAB: N31.1 (G), N34.1 (G), N53.1 (G), N54.1 (G), P31.1 (G), P33.1 (G), P42.1 (G), P55.1 (G), R41.1, TP120.1
FABs: N64.1 (G), N69.1 (G), N71.1 (G), N75.1 (G), P65.1 (G), P68.1 (G), P75.1 (G), P76.1 (G), R49.1, TP130.1
FACi: N32.1 (G), N42.1 (G), N51.1 (G), P34.1 (G), P43.1 (G), P54.1 (G), R40.1, TP119.1
FACis: N65.1 (G), N72.1 (G), N77.1 (G), P69.1 (G), P70.1 (G), P74.1 (G), R48.1, TP129.1
GND: D14.1 (K), D15.1 (K), N1.2 (S), N2.2 (S), N3.2 (S), N4.2 (S), N5.2 (S), N6.2 (S), N7.2 (S), N8.2 (S), N9.2 (S), N10.2 (S), N11.2 (S), N12.2 (S), N13.2 (S), N16.2 (S), N19.2 (S), N20.2 (S), N21.2 (S), N22.2 (S), N32.2 (S), N34.2 (S), N36.2 (S), N37.2 (S), N38.2 (S), N40.2 (S), N41.2 (S), N42.2 (S), N43.2 (S), N44.2 (S), N47.2 (S), N50.2 (S), N53.2 (S), N54.2 (S), N55.2 (S), N56.2 (S), N57.2 (S), N60.2 (S), N61.2 (S), N62.2 (S), N63.2 (S), N64.2 (S), N66.2 (S), N67.2 (S), N69.2 (S), N72.2 (S), N73.2 (S), N75.2 (S), N76.2 (S), N77.2 (S), R15.1, R16.1, R18.1, R20.2, R22.2, R23.2, R24.2, R25.2, R26.2, R30.2, R33.2, R34.2, R35.2, R36.2, R37.2, R38.2, R39.2, R40.2, R41.2, R42.2, R43.2, R44.2, R45.2, R46.2, R47.2, R48.2, R49.2, R50.2, R51.2, R52.2, TP6.1, TP7.1, TP9.1, TP17.1, TP23.1, TP28.1, TP36.1, TP39.1, TP97.1, TP98.1, TP99.1, TP100.1, TP101.1, TP102.1, TP111.1, TP116.1, TP123.1, TP128.1, TP135.1
unnamed: D1.1 (K), R3.1
unnamed: D2.1 (K), R4.1
unnamed: D3.1 (K), R5.1
unnamed: D4.1 (K), R6.1
unnamed: D5.1 (K), R10.1
unnamed: D6.1 (K), R14.1
unnamed: D7.1 (K), R19.1
unnamed: D8.1 (K), R21.1
unnamed: D9.2 (A), N23.2 (S), P24.2 (S), R19.2, TP31.1
unnamed: D9.1 (K), R20.1
unnamed: D10.2 (A), TP40.1
unnamed: D10.1 (K), R24.1
unnamed: D11.2 (A), TP41.1
unnamed: D11.1 (K), R25.1
unnamed: D12.2 (A), TP42.1
unnamed: D12.1 (K), R26.1
unnamed: D13.2 (A), N43.3 (D), N44.1 (G), N45.3 (D), N47.1 (G), P45.1 (G), P50.3 (D), P51.1 (G), TP105.1
unnamed: D13.1 (K), R30.1
unnamed: D14.2 (A), R31.1
unnamed: D15.2 (A), R32.1
unnamed: D16.2 (A), N43.1 (G), N44.3 (D), N48.3 (D), N50.1 (G), P48.1 (G), P50.1 (G), P51.3 (D), TP104.1
unnamed: D16.1 (K), R36.1
unnamed: D17.1 (K), R43.1
unnamed: D18.1 (K), R44.1
unnamed: D19.2 (A), N58.3 (D), N59.3 (D), P60.3 (D), P61.3 (D), TP126.1
unnamed: D19.1 (K), R45.1
unnamed: D20.1 (K), R51.1
unnamed: D21.1 (K), R52.1
unnamed: N3.3 (D), P3.3 (D), TP3.1
unnamed: N4.3 (D), N5.1 (G), P4.3 (D), P5.1 (G)
unnamed: N4.1 (G), N8.3 (D), P4.1 (G), P8.3 (D), R4.2
unnamed: N5.3 (D), N6.1 (G), P5.3 (D), P6.1 (G)
unnamed: N6.3 (D), N7.1 (G), P6.3 (D), P7.1 (G)
unnamed: N7.3 (D), N8.1 (G), P7.3 (D), P8.1 (G), TP4.1
unnamed: N10.3 (D), N11.1 (G), P10.3 (D), P11.1 (G)
unnamed: N9.3 (D), N10.1 (G), P9.3 (D), P10.1 (G)
unnamed: N11.3 (D), N12.1 (G), P11.3 (D), P12.1 (G)
unnamed: N12.3 (D), N13.1 (G), P12.3 (D), P13.1 (G), TP11.1
unnamed: N9.1 (G), N13.3 (D), P9.1 (G), P13.3 (D), R5.2
unnamed: N14.3 (D), P14.3 (D), P15.3 (D), P16.3 (D), R6.2, TP12.1
unnamed: N14.1 (G), P14.1 (G), R7.2, TP13.1
unnamed: N14.2 (S), N15.3 (D)
unnamed: N15.1 (G), P15.1 (G), R8.2, TP14.1
unnamed: N15.2 (S), N16.3 (D)
unnamed: N16.1 (G), P16.1 (G), R9.2, TP15.1
unnamed: N17.3 (D), P17.3 (D), P18.3 (D), P19.3 (D), R10.2, TP21.1
unnamed: N17.1 (G), P17.1 (G), R11.2, TP19.1
unnamed: N17.2 (S), N18.3 (D)
unnamed: N18.1 (G), P18.1 (G), R12.2, TP18.1
unnamed: N18.2 (S), N19.3 (D)
unnamed: N19.1 (G), P19.1 (G), R13.2, TP20.1
unnamed: N20.3 (D), N21.3 (D), P20.3 (D), R14.2, TP26.1
unnamed: N20.1 (G), P20.1 (G), R15.2, TP24.1
unnamed: N21.1 (G), P21.1 (G), R16.2, TP25.1
unnamed: N22.3 (D), N24.2 (S), N25.1 (G), P22.3 (D)
unnamed: N22.1 (G), P22.1 (G), P23.2 (S), P25.1 (G), R22.1, TP29.1
unnamed: N23.3 (D), P24.3 (D), TP30.1
unnamed: N23.1 (G), R18.2, TP33.1
unnamed: N24.3 (D), N25.3 (D), P23.3 (D), P25.3 (D), R21.2, TP37.1
unnamed: N24.1 (G), N25.2 (S), P23.1 (G), P25.2 (S), R23.1, TP34.1
unnamed: N26.3 (D), TP46.1
unnamed: N26.1 (G), TP48.1
unnamed: N26.2 (S), TP47.1
unnamed: N27.3 (D), TP71.1
unnamed: N27.1 (G), TP70.1
unnamed: N27.2 (S), TP72.1
unnamed: N28.3 (D), TP77.1
unnamed: N28.1 (G), TP76.1
unnamed: N28.2 (S), TP78.1
unnamed: N29.3 (D), TP83.1
unnamed: N29.1 (G), TP82.1
unnamed: N29.2 (S), TP84.1
unnamed: N30.3 (D), N33.3 (D), N56.1 (G), P41.3 (D), P42.3 (D), P56.1 (G)
unnamed: N30.2 (S), N31.3 (D)
unnamed: N31.2 (S), N32.3 (D)
unnamed: N33.2 (S), N34.3 (D), N41.3 (D), N42.3 (D)
unnamed: N35.3 (D), N37.3 (D), N38.1 (G), P37.3 (D), P38.1 (G), R31.2, TP106.1, TP107.1
unnamed: N35.1 (G), P39.1 (G), R34.1, TP108.1
unnamed: N35.2 (S), N36.3 (D)
unnamed: N36.1 (G), N40.1 (G), P35.1 (G), P40.1 (G), R35.1, TP110.1
unnamed: N37.1 (G), N38.3 (D), N39.3 (D), P37.1 (G), P38.3 (D), R32.2
unnamed: N39.1 (G), P36.1 (G), R33.1, TP109.1
unnamed: N39.2 (S), N40.3 (D)
unnamed: N45.1 (G), P44.1 (G), R37.1, TP113.1
unnamed: N45.2 (S), N46.3 (D)
unnamed: N46.1 (G), N49.1 (G), P46.1 (G), P47.1 (G), R39.1, TP103.1
unnamed: N46.2 (S), N47.3 (D)
unnamed: N48.1 (G), P49.1 (G), R38.1, TP114.1
unnamed: N48.2 (S), N49.3 (D)
unnamed: N49.2 (S), N50.3 (D)
unnamed: N51.2 (S), N54.3 (D), N55.3 (D)
unnamed: N52.2 (S), N53.3 (D)
unnamed: N58.1 (G), N62.3 (D), P58.1 (G), P62.3 (D)
unnamed: N58.2 (S), N60.3 (D)
unnamed: N59.1 (G), N62.1 (G), P61.1 (G), P62.1 (G), R47.1, TP124.1
unnamed: N59.2 (S), N61.3 (D)
unnamed: N60.1 (G), N63.3 (D), P59.1 (G), P63.3 (D)
unnamed: N61.1 (G), N63.1 (G), P60.1 (G), P63.1 (G), R46.1, TP125.1
unnamed: N64.3 (D), N65.2 (S), N66.3 (D)
unnamed: N68.2 (S), N69.3 (D)
unnamed: N70.3 (D), N74.3 (D), N76.1 (G), P71.3 (D), P75.3 (D), P77.1 (G)
unnamed: N70.2 (S), N71.3 (D)
unnamed: N71.2 (S), N72.3 (D)
unnamed: N73.3 (D), N74.2 (S), N75.3 (D), N77.3 (D)
unnamed: P20.2 (S), P21.3 (D)
unnamed: P24.1 (G), R17.1, TP32.1
unnamed: P26.3 (D), TP45.1
unnamed: P26.1 (G), TP44.1
unnamed: P26.2 (S), TP43.1
unnamed: P27.3 (D), TP69.1
unnamed: P27.1 (G), TP67.1
unnamed: P27.2 (S), TP68.1
unnamed: P28.3 (D), TP75.1
unnamed: P28.1 (G), TP73.1
unnamed: P28.2 (S), TP74.1
unnamed: P29.3 (D), TP81.1
unnamed: P29.1 (G), TP79.1
unnamed: P29.2 (S), TP80.1
unnamed: P30.3 (D), P31.2 (S), P33.3 (D), P34.2 (S)
unnamed: P31.3 (D), P32.2 (S)
unnamed: P35.3 (D), P36.3 (D), P38.2 (S)
unnamed: P37.2 (S), P39.3 (D), P40.3 (D)
unnamed: P41.2 (S), P52.2 (S), P53.3 (D), P54.3 (D), P55.3 (D)
unnamed: P42.2 (S), P43.3 (D)
unnamed: P43.2 (S), P52.3 (D)
unnamed: P44.3 (D), P45.3 (D), P46.3 (D), P50.2 (S)
unnamed: P47.3 (D), P48.3 (D), P49.3 (D), P51.2 (S)
unnamed: P58.3 (D), P59.3 (D), P60.2 (S), P61.2 (S)
unnamed: P64.3 (D), P65.2 (S), P68.3 (D), P69.2 (S)
unnamed: P65.3 (D), P66.2 (S)
unnamed: P70.3 (D), P71.2 (S), P72.3 (D), P73.2 (S), P76.3 (D)
unnamed: P73.3 (D), P74.2 (S)
unnamed: P74.3 (D), P75.2 (S)
unnamed: R27.1, TP49.1
unnamed: R27.2, TP50.1
unnamed: R28.1, TP51.1
unnamed: R28.2, TP52.1
unnamed: R29.1, TP53.1
unnamed: R29.2, TP54.1
unnamed: TP55.1, TP56.1, TP57.1, TP58.1, TP59.1, TP60.1
unnamed: TP61.1, TP62.1, TP63.1, TP64.1, TP65.1, TP66.1
unnamed: TP85.1, TP86.1, TP87.1, TP88.1, TP89.1, TP90.1
unnamed: TP91.1, TP92.1, TP93.1, TP94.1, TP95.1, TP96.1
SOUT: D18.2 (A), N56.3 (D), P56.3 (D), TP118.1
SOUTs: D21.2 (A), N76.3 (D), P77.3 (D), TP133.1
VDD: D1.2 (A), D2.2 (A), D3.2 (A), D4.2 (A), D5.2 (A), D6.2 (A), D7.2 (A), D8.2 (A), P1.2 (S), P2.2 (S), P3.2 (S), P4.2 (S), P5.2 (S), P6.2 (S), P7.2 (S), P8.2 (S), P9.2 (S), P10.2 (S), P11.2 (S), P12.2 (S), P13.2 (S), P14.2 (S), P15.2 (S), P16.2 (S), P17.2 (S), P18.2 (S), P19.2 (S), P21.2 (S), P22.2 (S), P30.2 (S), P33.2 (S), P35.2 (S), P36.2 (S), P39.2 (S), P40.2 (S), P44.2 (S), P45.2 (S), P46.2 (S), P47.2 (S), P48.2 (S), P49.2 (S), P53.2 (S), P54.2 (S), P55.2 (S), P56.2 (S), P57.2 (S), P58.2 (S), P59.2 (S), P62.2 (S), P63.2 (S), P64.2 (S), P67.2 (S), P68.2 (S), P70.2 (S), P72.2 (S), P76.2 (S), P77.2 (S), R7.1, R8.1, R9.1, R11.1, R12.1, R13.1, R17.2, TP5.1, TP8.1, TP10.1, TP16.1, TP22.1, TP27.1, TP35.1, TP38.1, TP112.1, TP115.1, TP122.1, TP127.1, TP134.1
X: N33.1 (G), N51.3 (D), N52.3 (D), N57.1 (G), P32.3 (D), P34.3 (D), P41.1 (G), P57.1 (G)
Xs: N65.3 (D), N67.1 (G), N68.3 (D), N74.1 (G), P66.3 (D), P67.1 (G), P69.3 (D), P71.1 (G)

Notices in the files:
parts and their libraries:
License: Apache-2.0
